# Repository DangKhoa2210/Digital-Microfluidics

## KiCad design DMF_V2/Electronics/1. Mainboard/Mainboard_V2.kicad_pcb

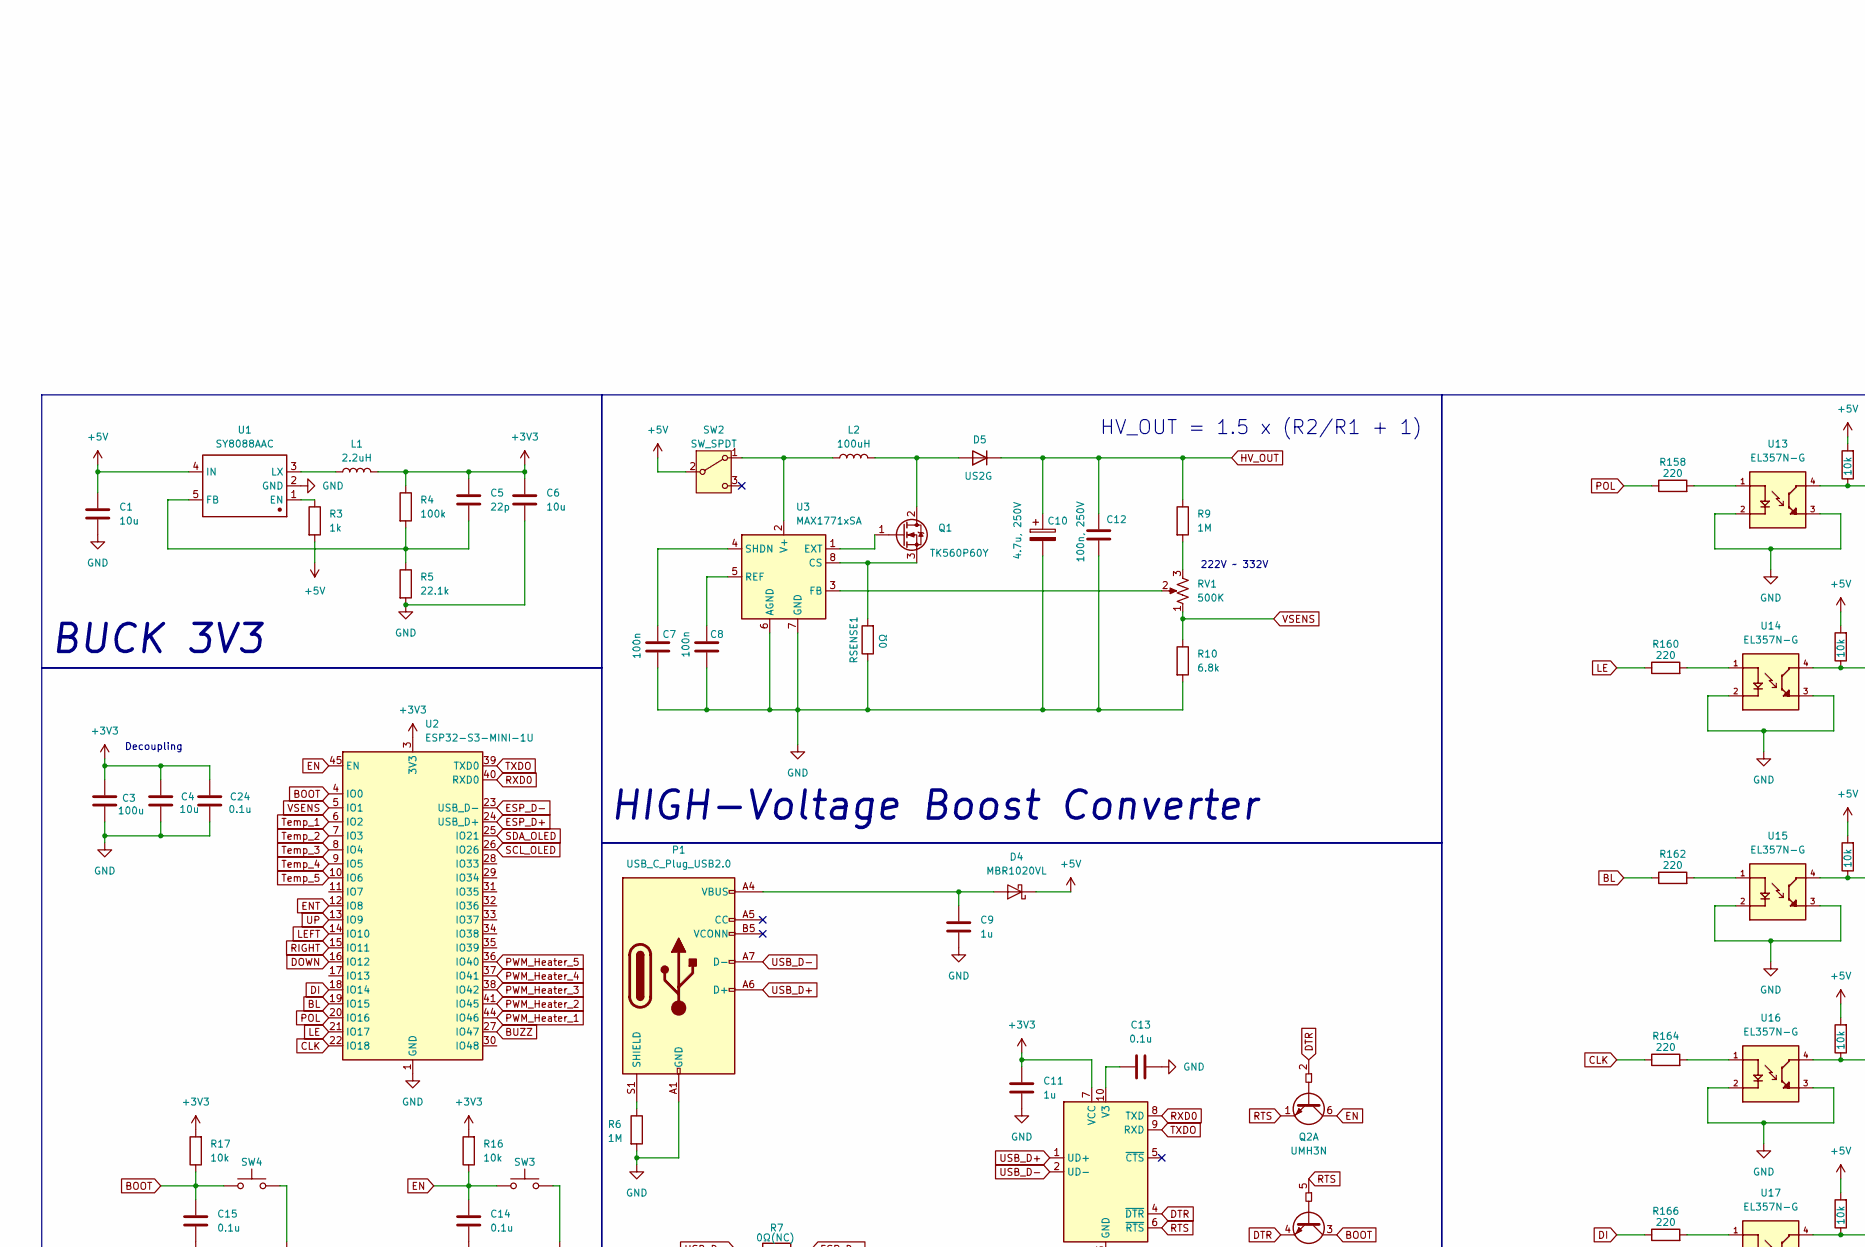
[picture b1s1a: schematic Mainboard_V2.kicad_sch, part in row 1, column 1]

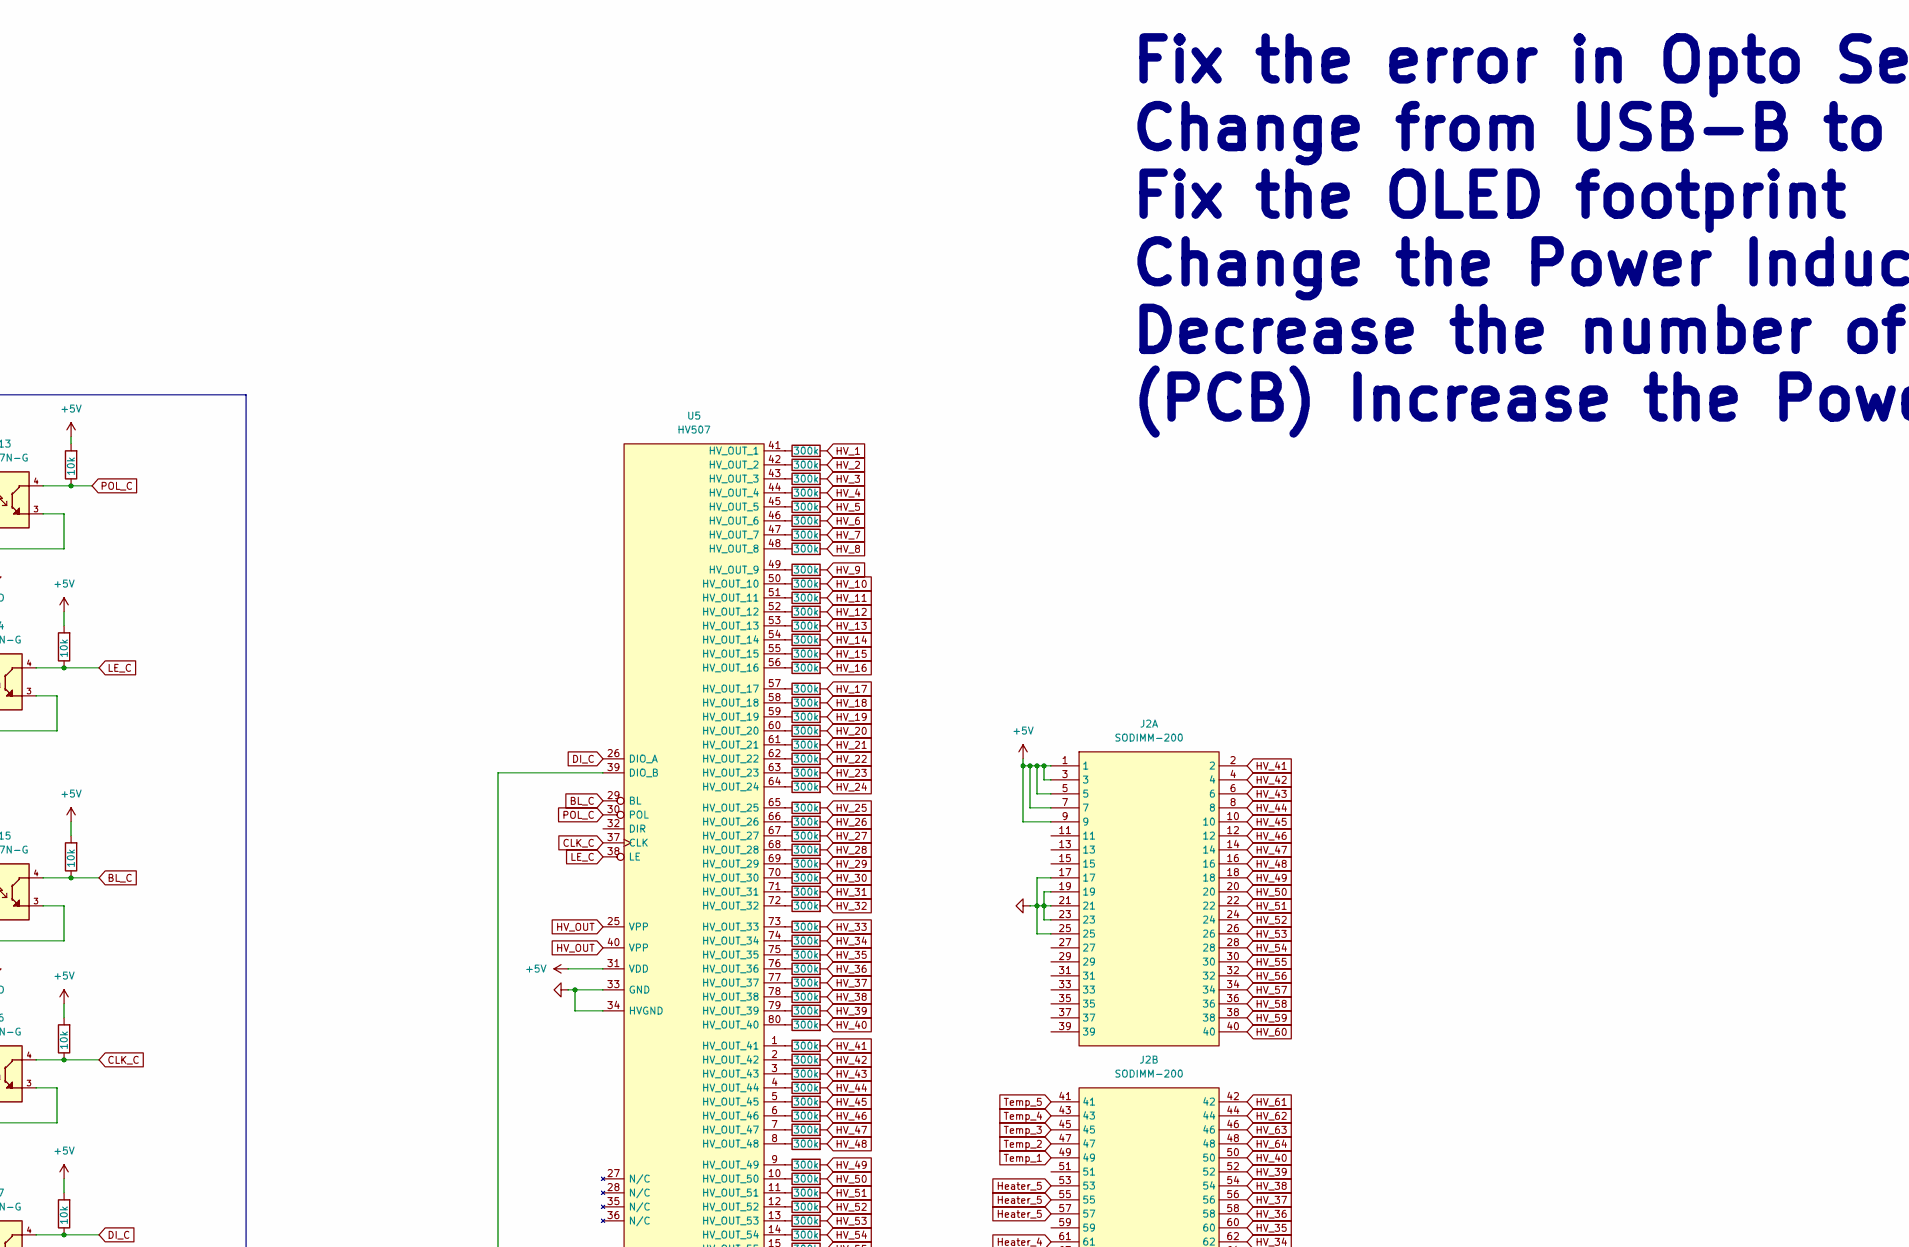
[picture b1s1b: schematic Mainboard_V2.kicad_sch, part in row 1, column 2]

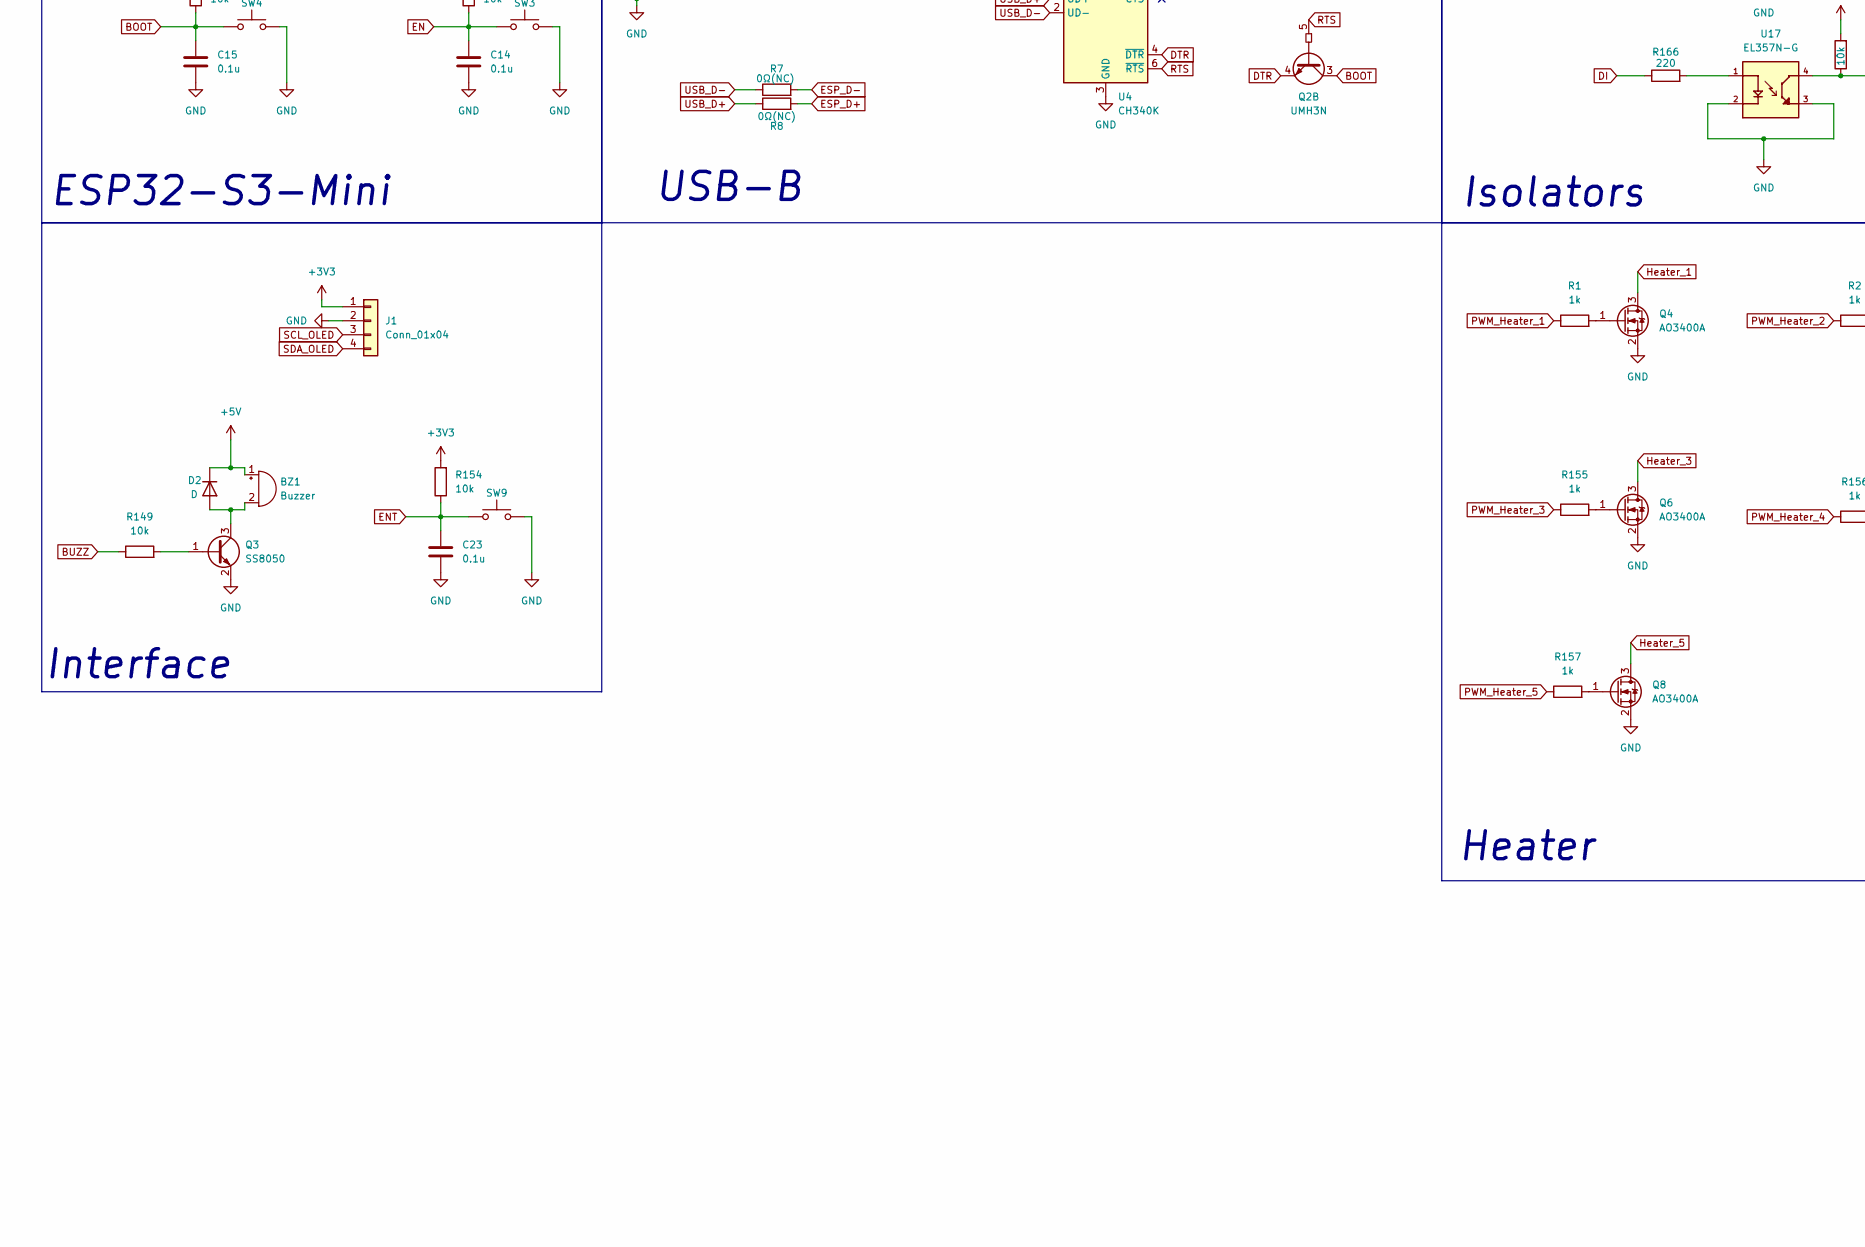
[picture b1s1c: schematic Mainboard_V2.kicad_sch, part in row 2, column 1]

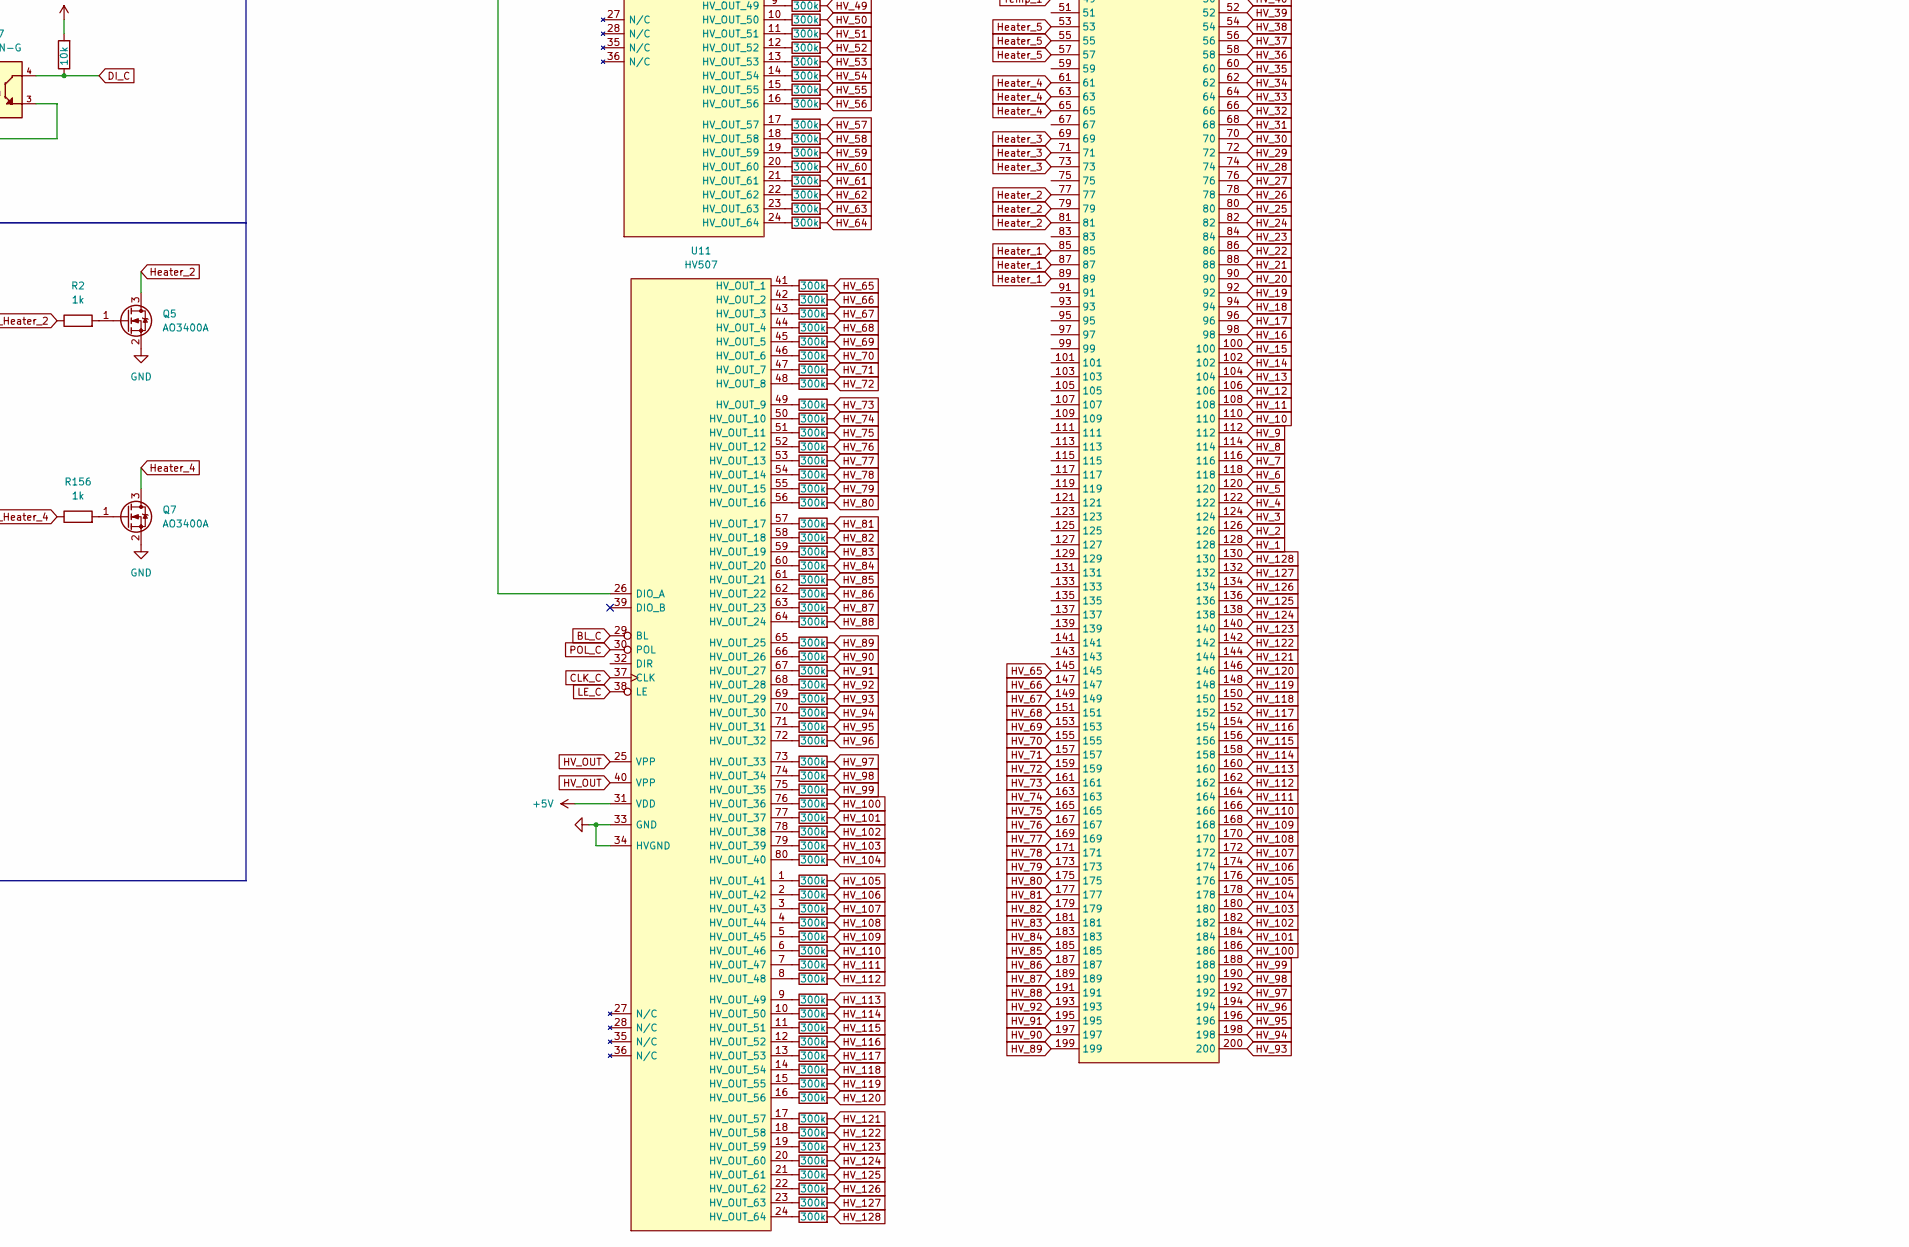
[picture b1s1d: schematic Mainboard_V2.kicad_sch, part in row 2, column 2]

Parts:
BZ1: Buzzer; Buzzer_12x9.5RM7.6
C1, C4, C6: 10u; C_0402_1005Metric
C3: 100u; C_0402_1005Metric
C5: 22p; C_0402_1005Metric
C7, C8: 100n; C_0402_1005Metric
C9, C11: 1u; C_0402_1005Metric
C10: 4.7u, 250V; CP_Radial_D8.0mm_P3.50mm
C12: 100n, 250V; C_Rect_L13.0mm_W6.5mm_P7.50mm_P10.00mm
C13, C14, C15, C23, C24: 0.1u; C_0402_1005Metric
D2: D; D_0201_0603Metric
D4: MBR1020VL; D_SOD-123F
D5: US2G; D_SMB
J1: Conn_01x04; FanPinHeader_1x04_P2.54mm_Vertical
J2: SODIMM-200; SO-DIMM
L1: 2.2uH; PowerInductor_CYA0630-2.2UH
L2: 100uH; PowerInductor_CYA0630-2.2UH
P1: USB_C_Plug_USB2.0; USB_C_Receptacle_Amphenol_124019772112A
Q1: TK560P60Y; TO-252-2
Q2: UMH3N; SOT-363_SC-70-6
Q3: SS8050; SOT-23
Q4, Q5, Q6, Q7, Q8: AO3400A; SOT-23
R1, R2, R3, R155, R156, R157: 1k; R_0402_1005Metric
R4: 100k; R_0402_1005Metric
R5: 22.1k; R_0402_1005Metric
R6: 1M; R_0402_1005Metric
R7, R8: 0Ω(NC); R_0402_1005Metric
R9: 1M; R_0805_2012Metric
R10: 6.8k; R_0402_1005Metric
R16, R17, R149, R154, R159, R161, R163, R165, R167: 10k; R_0402_1005Metric
R20, R21, R22, R23, R24, R25, R26, R27, R28, R29, R30, R31, R32, R33, R34, R35, R36, R37, R38, R39, R40, R41, R42, R43, R44, R45, R46, R47, R48, R49, R50, R51, R52, R53, R54, R55, R56, R57, R58, R59, R60, R61, R62, R63, R64, R65, R66, R67, R68, R69, R70, R71, R72, R73, R74, R75, R76, R77, R78, R79, R80, R81, R82, R83, R84, R85, R86, R87, R88, R89, R90, R91, R92, R93, R94, R95, R96, R97, R98, R99, R100, R101, R102, R103, R104, R105, R106, R107, R108, R109, R110, R111, R112, R113, R114, R115, R116, R117, R118, R119, R120, R121, R122, R123, R124, R125, R126, R127, R128, R129, R130, R131, R132, R133, R134, R135, R136, R137, R138, R139, R140, R141, R142, R143, R144, R145, R146, R147: 300k; R_0402_1005Metric
R158, R160, R162, R164, R166: 220; R_0402_1005Metric
RSENSE1: 0Ω; R_0402_1005Metric
RV1: 500K; Potentiometer_Bourns_3296W_Vertical
SW2: SW_SPDT; SW_Slide-03_Wuerth-WS-SLTV_10x2.5x6.4_P2.54mm
SW3, SW4, SW9: SW_Push; SW_SPST_TL3342
U1: SY8088AAC; SY8088
U2: ESP32-S3-MINI-1U; ESP32-S2-MINI-1
U3: MAX1771xSA; SO-8_3.9x4.9mm_P1.27mm
U4: CH340K; SSOP-10-1EP_3.9x4.9mm_P1mm_EP2.1x3.3mm
U5, U11: HV507; HV507PG-G
U13, U14, U15, U16, U17: EL357N-G; OPTO_EL357N-G; PARTREV 6

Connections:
+3V3: C3.1, C4.1, C5.1, C6.1, C11.1, C24.1, J1.1, L1.2, R4.1, R16.2, R17.2, R154.2, U2.3 (3V3), U4.7 (VCC)
+5V: BZ1.1 (+), C1.1, D2.1 (K), D4.1 (K), J2.1, J2.3, J2.5, J2.7, J2.9, R3.2, R159.2, R161.2, R163.2, R165.2, R167.2, SW2.2 (B), U1.4 (IN), U5.31 (VDD), U11.31 (VDD)
BL: R162.1, U2.19 (IO15)
BL_C: R163.1, U5.29 (BL), U11.29 (BL), U15.4
BOOT: C15.1, Q2.3 (C2), R17.1, SW4.1, U2.4 (IO0)
BUZZ: R149.1, U2.27 (IO47)
CLK: R164.1, U2.22 (IO18)
CLK_C: R165.1, U5.37 (CLK), U11.37 (CLK), U16.4
DI: R166.1, U2.18 (IO14)
DI_C: R167.1, U5.26 (DIO_A), U17.4
DOWN: U2.16 (IO12)
DTR: Q2.2 (B1), Q2.4 (E2), U4.4 (~DTR)
EN: C14.1, Q2.6 (C1), R16.1, SW3.1, U2.45 (EN)
ENT: C23.1, R154.1, SW9.1, U2.12 (IO8)
ESP_D+: R8.2, U2.24 (USB_D+)
ESP_D-: R7.2, U2.23 (USB_D-)
GND: C1.2, C3.2, C4.2, C6.2, C7.2, C8.2, C9.2, C10.2, C11.2, C12.2, C13.2, C14.2, C15.2, C23.2, C24.2, J1.2, J2.17, J2.19, J2.21, J2.23, J2.25, P1.A1 (GND), P1.A12 (GND), P1.B1 (GND), P1.B12 (GND), Q3.2 (E), Q4.2 (S), Q5.2 (S), Q6.2 (S), Q7.2 (S), Q8.2 (S), R5.2, R6.2, R10.2, RSENSE1.1, SW3.2, SW4.2, SW9.2, U1.2 (GND), U2.1 (GND), U2.2 (GND), U2.42 (GND), U2.43 (GND), U2.46 (GND), U2.47 (GND), U2.48 (GND), U2.49 (GND), U2.50 (GND), U2.51 (GND), U2.52 (GND), U2.53 (GND), U2.54 (GND), U2.55 (GND), U2.56 (GND), U2.57 (GND), U2.58 (GND), U2.59 (GND), U2.60 (GND), U2.61 (GND), U2.62 (GND), U2.63 (GND), U2.64 (GND), U2.65 (GND), U3.6 (AGND), U3.7 (GND), U4.3 (GND), U4.11 (GND), U5.33 (GND), U5.34 (HVGND), U11.33 (GND), U11.34 (HVGND), U13.2, U13.3, U14.2, U14.3, U15.2, U15.3, U16.2, U16.3, U17.2, U17.3
HV_1: J2.128, R20.2
HV_2: J2.126, R21.2
HV_3: J2.124, R22.2
HV_4: J2.122, R23.2
HV_5: J2.120, R24.2
HV_6: J2.118, R25.2
HV_7: J2.116, R26.2
HV_8: J2.114, R27.2
HV_9: J2.112, R28.2
HV_10: J2.110, R29.2
HV_11: J2.108, R30.2
HV_12: J2.106, R31.2
HV_13: J2.104, R32.2
HV_14: J2.102, R33.2
HV_15: J2.100, R34.2
HV_16: J2.98, R35.2
HV_17: J2.96, R36.2
HV_18: J2.94, R37.2
HV_19: J2.92, R38.2
HV_20: J2.90, R39.2
HV_21: J2.88, R40.2
HV_22: J2.86, R41.2
HV_23: J2.84, R42.2
HV_24: J2.82, R43.2
HV_25: J2.80, R44.2
HV_26: J2.78, R45.2
HV_27: J2.76, R46.2
HV_28: J2.74, R47.2
HV_29: J2.72, R48.2
HV_30: J2.70, R49.2
HV_31: J2.68, R50.2
HV_32: J2.66, R51.2
HV_33: J2.64, R52.2
HV_34: J2.62, R53.2
HV_35: J2.60, R54.2
HV_36: J2.58, R55.2
HV_37: J2.56, R56.2
HV_38: J2.54, R57.2
HV_39: J2.52, R58.2
HV_40: J2.50, R59.2
HV_41: J2.2, R60.2
HV_42: J2.4, R61.2
HV_43: J2.6, R62.2
HV_44: J2.8, R63.2
HV_45: J2.10, R64.2
HV_46: J2.12, R65.2
HV_47: J2.14, R66.2
HV_48: J2.16, R67.2
HV_49: J2.18, R68.2
HV_50: J2.20, R69.2
HV_51: J2.22, R70.2
HV_52: J2.24, R71.2
HV_53: J2.26, R72.2
HV_54: J2.28, R73.2
HV_55: J2.30, R74.2
HV_56: J2.32, R75.2
HV_57: J2.34, R76.2
HV_58: J2.36, R77.2
HV_59: J2.38, R78.2
HV_60: J2.40, R79.2
HV_61: J2.42, R80.2
HV_62: J2.44, R81.2
HV_63: J2.46, R82.2
HV_64: J2.48, R83.2
HV_65: J2.145, R84.2
HV_66: J2.147, R85.2
HV_67: J2.149, R86.2
HV_68: J2.151, R87.2
HV_69: J2.153, R88.2
HV_70: J2.155, R89.2
HV_71: J2.157, R90.2
HV_72: J2.159, R91.2
HV_73: J2.161, R92.2
HV_74: J2.163, R93.2
HV_75: J2.165, R94.2
HV_76: J2.167, R95.2
HV_77: J2.169, R96.2
HV_78: J2.171, R97.2
HV_79: J2.173, R98.2
HV_80: J2.175, R99.2
HV_81: J2.177, R100.2
HV_82: J2.179, R101.2
HV_83: J2.181, R102.2
HV_84: J2.183, R103.2
HV_85: J2.185, R104.2
HV_86: J2.187, R105.2
HV_87: J2.189, R106.2
HV_88: J2.191, R107.2
HV_89: J2.199, R108.2
HV_90: J2.197, R109.2
HV_91: J2.195, R110.2
HV_92: J2.193, R111.2
HV_93: J2.200, R112.2
HV_94: J2.198, R113.2
HV_95: J2.196, R114.2
HV_96: J2.194, R115.2
HV_97: J2.192, R116.2
HV_98: J2.190, R117.2
HV_99: J2.188, R118.2
HV_100: J2.186, R119.2
HV_101: J2.184, R120.2
HV_102: J2.182, R121.2
HV_103: J2.180, R122.2
HV_104: J2.178, R123.2
HV_105: J2.176, R124.2
HV_106: J2.174, R125.2
HV_107: J2.172, R126.2
HV_108: J2.170, R127.2
HV_109: J2.168, R128.2
HV_110: J2.166, R129.2
HV_111: J2.164, R130.2
HV_112: J2.162, R131.2
HV_113: J2.160, R132.2
HV_114: J2.158, R133.2
HV_115: J2.156, R134.2
HV_116: J2.154, R135.2
HV_117: J2.152, R136.2
HV_118: J2.150, R137.2
HV_119: J2.148, R138.2
HV_120: J2.146, R139.2
HV_121: J2.144, R140.2
HV_122: J2.142, R141.2
HV_123: J2.140, R142.2
HV_124: J2.138, R143.2
HV_125: J2.136, R144.2
HV_126: J2.134, R145.2
HV_127: J2.132, R146.2
HV_128: J2.130, R147.2
HV_OUT: C10.1, C12.1, D5.1 (K), R9.1, U5.25 (VPP), U5.40 (VPP), U11.25 (VPP), U11.40 (VPP)
Heater_1: J2.85, J2.87, J2.89, Q4.3 (D)
Heater_2: J2.77, J2.79, J2.81, Q5.3 (D)
Heater_3: J2.69, J2.71, J2.73, Q6.3 (D)
Heater_4: J2.61, J2.63, J2.65, Q7.3 (D)
Heater_5: J2.53, J2.55, J2.57, Q8.3 (D)
LE: R160.1, U2.21 (IO17)
LEFT: U2.14 (IO10)
LE_C: R161.1, U5.38 (LE), U11.38 (LE), U14.4
unnamed: BZ1.2 (-), D2.2 (A), Q3.3 (C)
unnamed: C9.1, D4.2 (A), P1.A4 (VBUS), P1.A9 (VBUS), P1.B4 (VBUS), P1.B9 (VBUS)
unnamed: D5.2 (A), L2.2, Q1.2 (D)
unnamed: P1.S1 (SHIELD), R6.1
unnamed: Q1.1 (G), U3.1 (EXT)
unnamed: Q1.3 (S), RSENSE1.2, U3.8 (CS)
unnamed: Q3.1 (B), R149.2
unnamed: Q4.1 (G), R1.2
unnamed: Q5.1 (G), R2.2
unnamed: Q6.1 (G), R155.2
unnamed: Q7.1 (G), R156.2
unnamed: Q8.1 (G), R157.2
unnamed: R9.2, RV1.3
unnamed: R158.2, U13.1
unnamed: R160.2, U14.1
unnamed: R162.2, U15.1
unnamed: R164.2, U16.1
unnamed: R166.2, U17.1
unnamed: L2.1, SW2.1 (A), U3.2 (V+)
unnamed: R3.1, U1.1 (EN)
unnamed: C5.2, R4.2, R5.1, U1.5 (FB)
unnamed: L1.1, U1.3 (LX)
unnamed: RV1.2, U3.3 (FB)
unnamed: C8.1, U3.5 (REF)
unnamed: C7.1, U3.4 (SHDN)
unnamed: C13.1, U4.10 (V3)
unnamed: R20.1, U5.41 (HV_OUT_1)
unnamed: R21.1, U5.42 (HV_OUT_2)
unnamed: R22.1, U5.43 (HV_OUT_3)
unnamed: R23.1, U5.44 (HV_OUT_4)
unnamed: R24.1, U5.45 (HV_OUT_5)
unnamed: R25.1, U5.46 (HV_OUT_6)
unnamed: R26.1, U5.47 (HV_OUT_7)
unnamed: R27.1, U5.48 (HV_OUT_8)
unnamed: R28.1, U5.49 (HV_OUT_9)
unnamed: R29.1, U5.50 (HV_OUT_10)
unnamed: R30.1, U5.51 (HV_OUT_11)
unnamed: R31.1, U5.52 (HV_OUT_12)
unnamed: R32.1, U5.53 (HV_OUT_13)
unnamed: R33.1, U5.54 (HV_OUT_14)
unnamed: R34.1, U5.55 (HV_OUT_15)
unnamed: R35.1, U5.56 (HV_OUT_16)
unnamed: R36.1, U5.57 (HV_OUT_17)
unnamed: R37.1, U5.58 (HV_OUT_18)
unnamed: R38.1, U5.59 (HV_OUT_19)
unnamed: R39.1, U5.60 (HV_OUT_20)
unnamed: R40.1, U5.61 (HV_OUT_21)
unnamed: R41.1, U5.62 (HV_OUT_22)
unnamed: R42.1, U5.63 (HV_OUT_23)
unnamed: R43.1, U5.64 (HV_OUT_24)
unnamed: R44.1, U5.65 (HV_OUT_25)
unnamed: R45.1, U5.66 (HV_OUT_26)
unnamed: R46.1, U5.67 (HV_OUT_27)
unnamed: R47.1, U5.68 (HV_OUT_28)
unnamed: R48.1, U5.69 (HV_OUT_29)
unnamed: R49.1, U5.70 (HV_OUT_30)
unnamed: R50.1, U5.71 (HV_OUT_31)
unnamed: R51.1, U5.72 (HV_OUT_32)
unnamed: R52.1, U5.73 (HV_OUT_33)
unnamed: R53.1, U5.74 (HV_OUT_34)
unnamed: R54.1, U5.75 (HV_OUT_35)
unnamed: R55.1, U5.76 (HV_OUT_36)
unnamed: R56.1, U5.77 (HV_OUT_37)
unnamed: R57.1, U5.78 (HV_OUT_38)
unnamed: R58.1, U5.79 (HV_OUT_39)
unnamed: R59.1, U5.80 (HV_OUT_40)
unnamed: R60.1, U5.1 (HV_OUT_41)
unnamed: R61.1, U5.2 (HV_OUT_42)
unnamed: R62.1, U5.3 (HV_OUT_43)
unnamed: R63.1, U5.4 (HV_OUT_44)
unnamed: R64.1, U5.5 (HV_OUT_45)
unnamed: R65.1, U5.6 (HV_OUT_46)
unnamed: R66.1, U5.7 (HV_OUT_47)
unnamed: R67.1, U5.8 (HV_OUT_48)
unnamed: R68.1, U5.9 (HV_OUT_49)
unnamed: R69.1, U5.10 (HV_OUT_50)
unnamed: R70.1, U5.11 (HV_OUT_51)
unnamed: R71.1, U5.12 (HV_OUT_52)
unnamed: R72.1, U5.13 (HV_OUT_53)
unnamed: R73.1, U5.14 (HV_OUT_54)
unnamed: R74.1, U5.15 (HV_OUT_55)
unnamed: R75.1, U5.16 (HV_OUT_56)
unnamed: R76.1, U5.17 (HV_OUT_57)
unnamed: R77.1, U5.18 (HV_OUT_58)
unnamed: R78.1, U5.19 (HV_OUT_59)
unnamed: R79.1, U5.20 (HV_OUT_60)
unnamed: R80.1, U5.21 (HV_OUT_61)
unnamed: R81.1, U5.22 (HV_OUT_62)
unnamed: R82.1, U5.23 (HV_OUT_63)
unnamed: R83.1, U5.24 (HV_OUT_64)
unnamed: U5.39 (DIO_B), U11.26 (DIO_A)
unnamed: R84.1, U11.41 (HV_OUT_1)
unnamed: R85.1, U11.42 (HV_OUT_2)
unnamed: R86.1, U11.43 (HV_OUT_3)
unnamed: R87.1, U11.44 (HV_OUT_4)
unnamed: R88.1, U11.45 (HV_OUT_5)
unnamed: R89.1, U11.46 (HV_OUT_6)
unnamed: R90.1, U11.47 (HV_OUT_7)
unnamed: R91.1, U11.48 (HV_OUT_8)
unnamed: R92.1, U11.49 (HV_OUT_9)
unnamed: R93.1, U11.50 (HV_OUT_10)
unnamed: R94.1, U11.51 (HV_OUT_11)
unnamed: R95.1, U11.52 (HV_OUT_12)
unnamed: R96.1, U11.53 (HV_OUT_13)
unnamed: R97.1, U11.54 (HV_OUT_14)
unnamed: R98.1, U11.55 (HV_OUT_15)
unnamed: R99.1, U11.56 (HV_OUT_16)
unnamed: R100.1, U11.57 (HV_OUT_17)
unnamed: R101.1, U11.58 (HV_OUT_18)
unnamed: R102.1, U11.59 (HV_OUT_19)
unnamed: R103.1, U11.60 (HV_OUT_20)
unnamed: R104.1, U11.61 (HV_OUT_21)
unnamed: R105.1, U11.62 (HV_OUT_22)
unnamed: R106.1, U11.63 (HV_OUT_23)
unnamed: R107.1, U11.64 (HV_OUT_24)
unnamed: R108.1, U11.65 (HV_OUT_25)
unnamed: R109.1, U11.66 (HV_OUT_26)
unnamed: R110.1, U11.67 (HV_OUT_27)
unnamed: R111.1, U11.68 (HV_OUT_28)
unnamed: R112.1, U11.69 (HV_OUT_29)
unnamed: R113.1, U11.70 (HV_OUT_30)
unnamed: R114.1, U11.71 (HV_OUT_31)
unnamed: R115.1, U11.72 (HV_OUT_32)
unnamed: R116.1, U11.73 (HV_OUT_33)
unnamed: R117.1, U11.74 (HV_OUT_34)
unnamed: R118.1, U11.75 (HV_OUT_35)
unnamed: R119.1, U11.76 (HV_OUT_36)
unnamed: R120.1, U11.77 (HV_OUT_37)
unnamed: R121.1, U11.78 (HV_OUT_38)
unnamed: R122.1, U11.79 (HV_OUT_39)
unnamed: R123.1, U11.80 (HV_OUT_40)
unnamed: R124.1, U11.1 (HV_OUT_41)
unnamed: R125.1, U11.2 (HV_OUT_42)
unnamed: R126.1, U11.3 (HV_OUT_43)
unnamed: R127.1, U11.4 (HV_OUT_44)
unnamed: R128.1, U11.5 (HV_OUT_45)
unnamed: R129.1, U11.6 (HV_OUT_46)
unnamed: R130.1, U11.7 (HV_OUT_47)
unnamed: R131.1, U11.8 (HV_OUT_48)
unnamed: R132.1, U11.9 (HV_OUT_49)
unnamed: R133.1, U11.10 (HV_OUT_50)
unnamed: R134.1, U11.11 (HV_OUT_51)
unnamed: R135.1, U11.12 (HV_OUT_52)
unnamed: R136.1, U11.13 (HV_OUT_53)
unnamed: R137.1, U11.14 (HV_OUT_54)
unnamed: R138.1, U11.15 (HV_OUT_55)
unnamed: R139.1, U11.16 (HV_OUT_56)
unnamed: R140.1, U11.17 (HV_OUT_57)
unnamed: R141.1, U11.18 (HV_OUT_58)
unnamed: R142.1, U11.19 (HV_OUT_59)
unnamed: R143.1, U11.20 (HV_OUT_60)
unnamed: R144.1, U11.21 (HV_OUT_61)
unnamed: R145.1, U11.22 (HV_OUT_62)
unnamed: R146.1, U11.23 (HV_OUT_63)
unnamed: R147.1, U11.24 (HV_OUT_64)
POL: R158.1, U2.20 (IO16)
POL_C: R159.1, U5.30 (POL), U11.30 (POL), U13.4
PWM_Heater_1: R1.1, U2.44 (IO46)
PWM_Heater_2: R2.1, U2.41 (IO45)
PWM_Heater_3: R155.1, U2.38 (IO42)
PWM_Heater_4: R156.1, U2.37 (IO41)
PWM_Heater_5: R157.1, U2.36 (IO40)
RIGHT: U2.15 (IO11)
RTS: Q2.1 (E1), Q2.5 (B2), U4.6 (~RTS)
RXD0: U2.40 (RXD0), U4.8 (TXD)
SCL_OLED: J1.3, U2.26 (IO26)
SDA_OLED: J1.4, U2.25 (IO21)
TXDO: U2.39 (TXD0), U4.9 (RXD)
Temp_1: J2.49, U2.6 (IO2)
Temp_2: J2.47, U2.7 (IO3)
Temp_3: J2.45, U2.8 (IO4)
Temp_4: J2.43, U2.9 (IO5)
Temp_5: J2.41, U2.10 (IO6)
UP: U2.13 (IO9)
USB_D+: P1.A6 (D+), R8.1, U4.1 (UD+)
USB_D-: P1.A7 (D-), R7.1, U4.2 (UD-)
VSENS: R10.1, RV1.1, U2.5 (IO1)

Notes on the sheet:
Heater
USB-B
Interface
Decoupling
HV_OUT = 1.5 x (R2/R1 + 1)
222V ~ 332V
Fix the error in Opto Series Change from USB-B to USB-C Fix the OLED footprint Change the Power Inductor footprint Decrease the number of Buttons, use smaller button's footprint (PCB) Increase the Power traces width
ESP32-S3-Mini
Isolators
BUCK 3V3
HIGH-Voltage Boost Converter

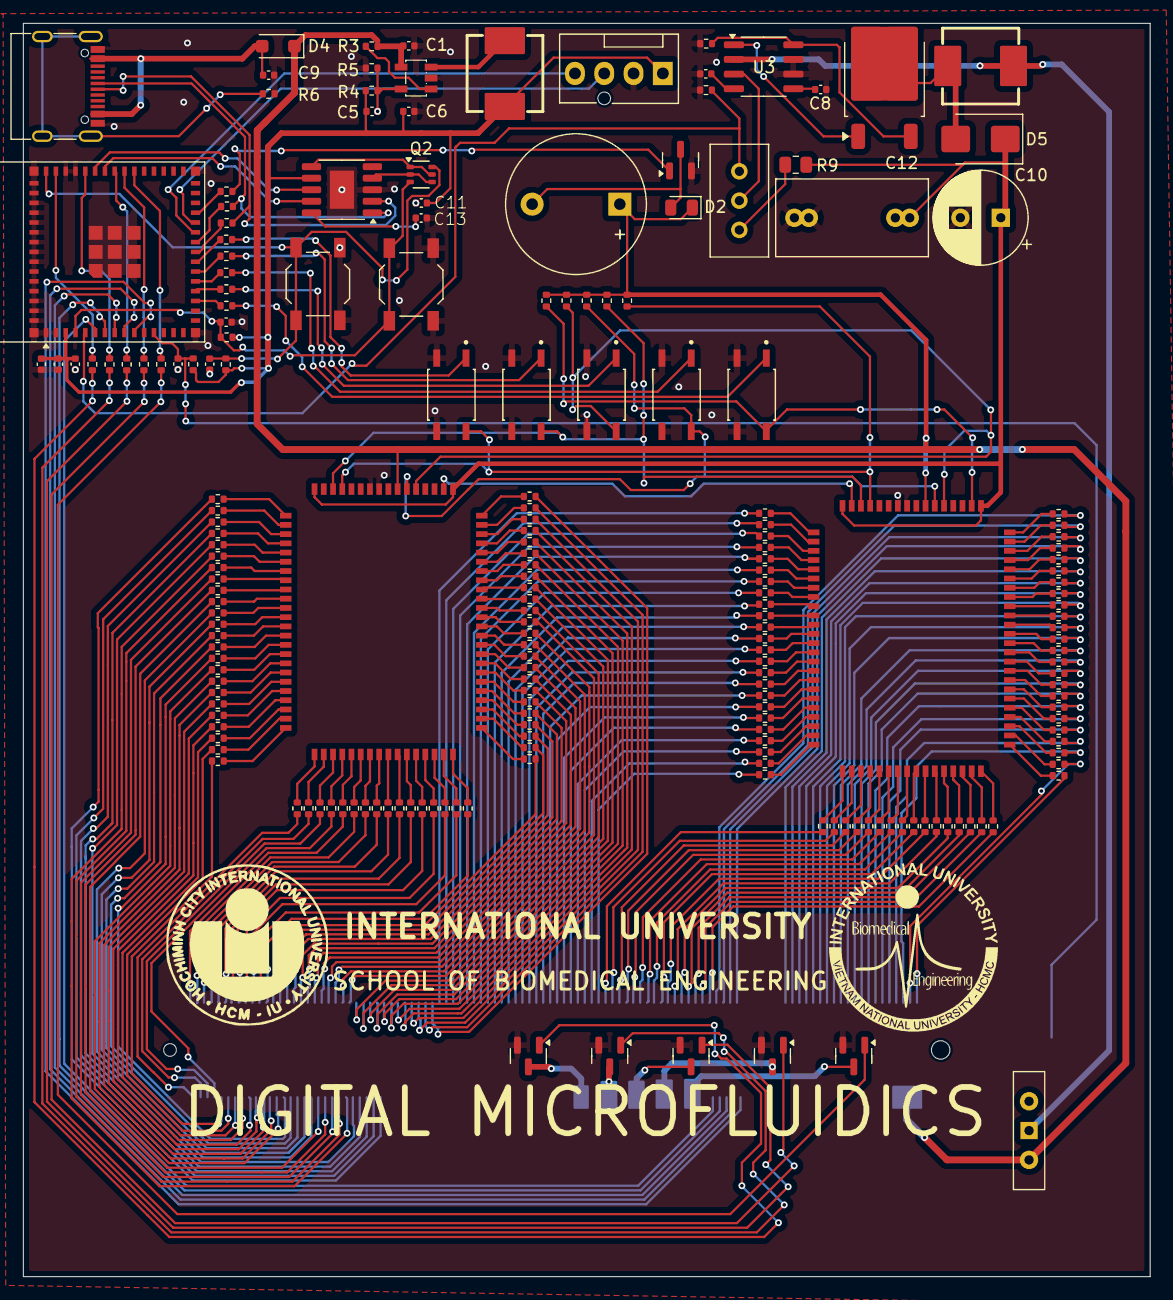
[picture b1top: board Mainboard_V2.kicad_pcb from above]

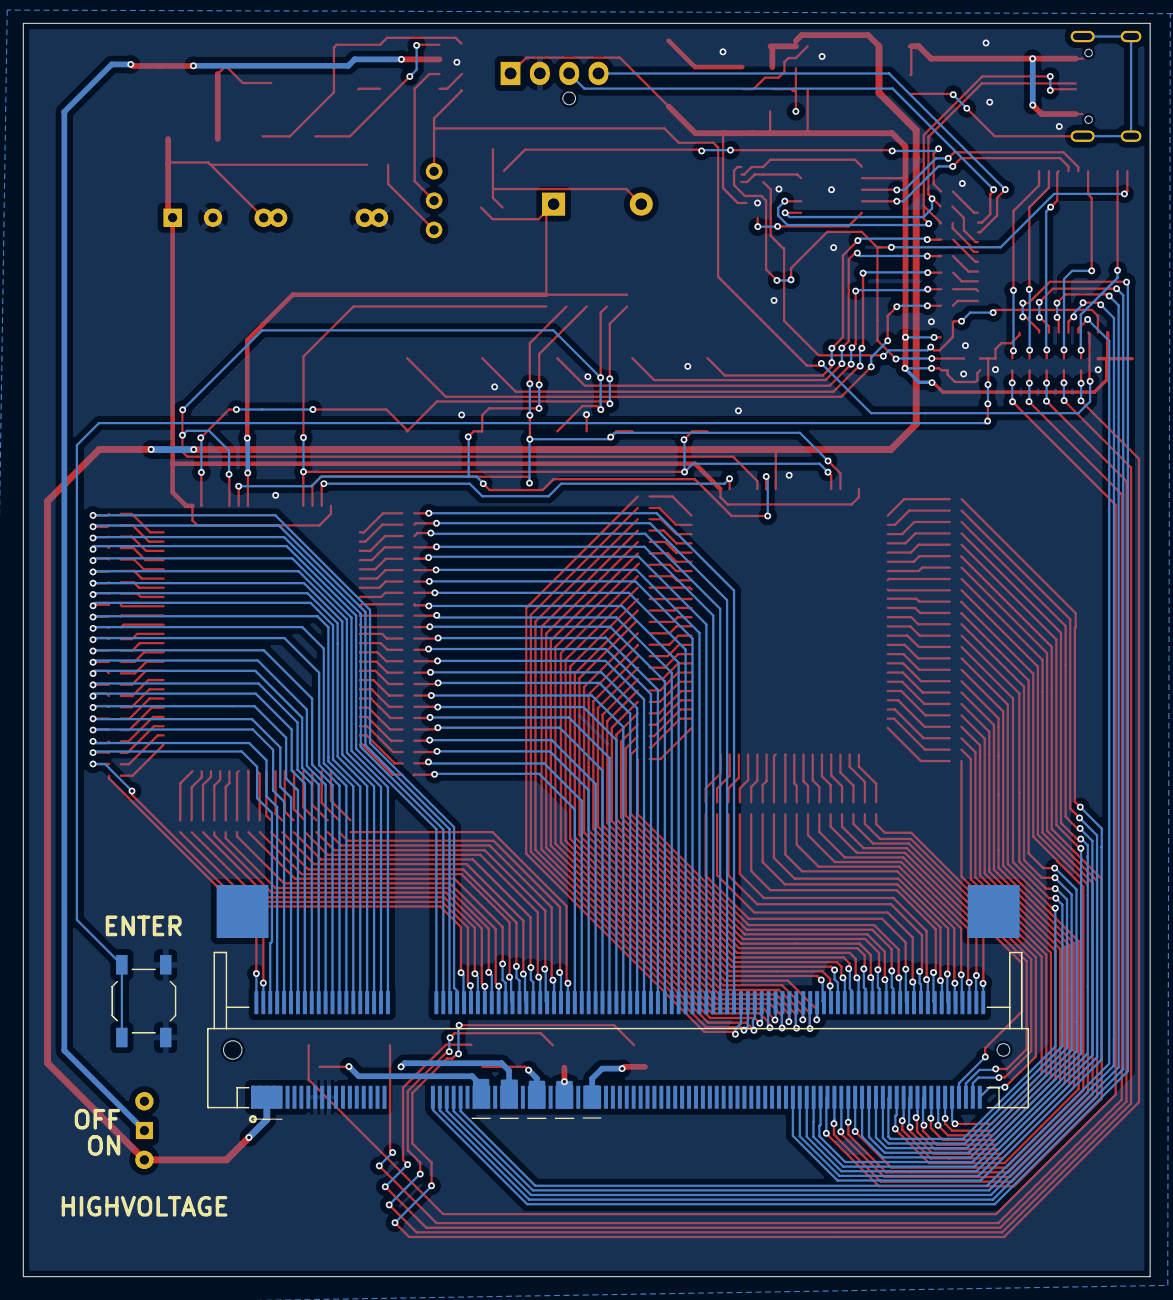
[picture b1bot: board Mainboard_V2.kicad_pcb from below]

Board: 2 copper layers, 97.7 x 108.6 mm, 205 parts (2 on the bottom side), 327 nets.
